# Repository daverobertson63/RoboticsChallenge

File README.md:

# RoboticsChallenge
Barclays Robotics Challenge - Main Code Repo

This is the main repo for the Barclays Remote Challenge and will work on any Unbutu style build

To install open a terminal window and make sure you are in /home/username - this is /home/roboteer

wget -N https://raw.githubusercontent.com/daverobertson63/RoboticsChallenge/master/brc.sh

chmod +x ./brc.sh

./brc.sh

Follow the instructions for either a local or remote refresh.  Local is the default one.

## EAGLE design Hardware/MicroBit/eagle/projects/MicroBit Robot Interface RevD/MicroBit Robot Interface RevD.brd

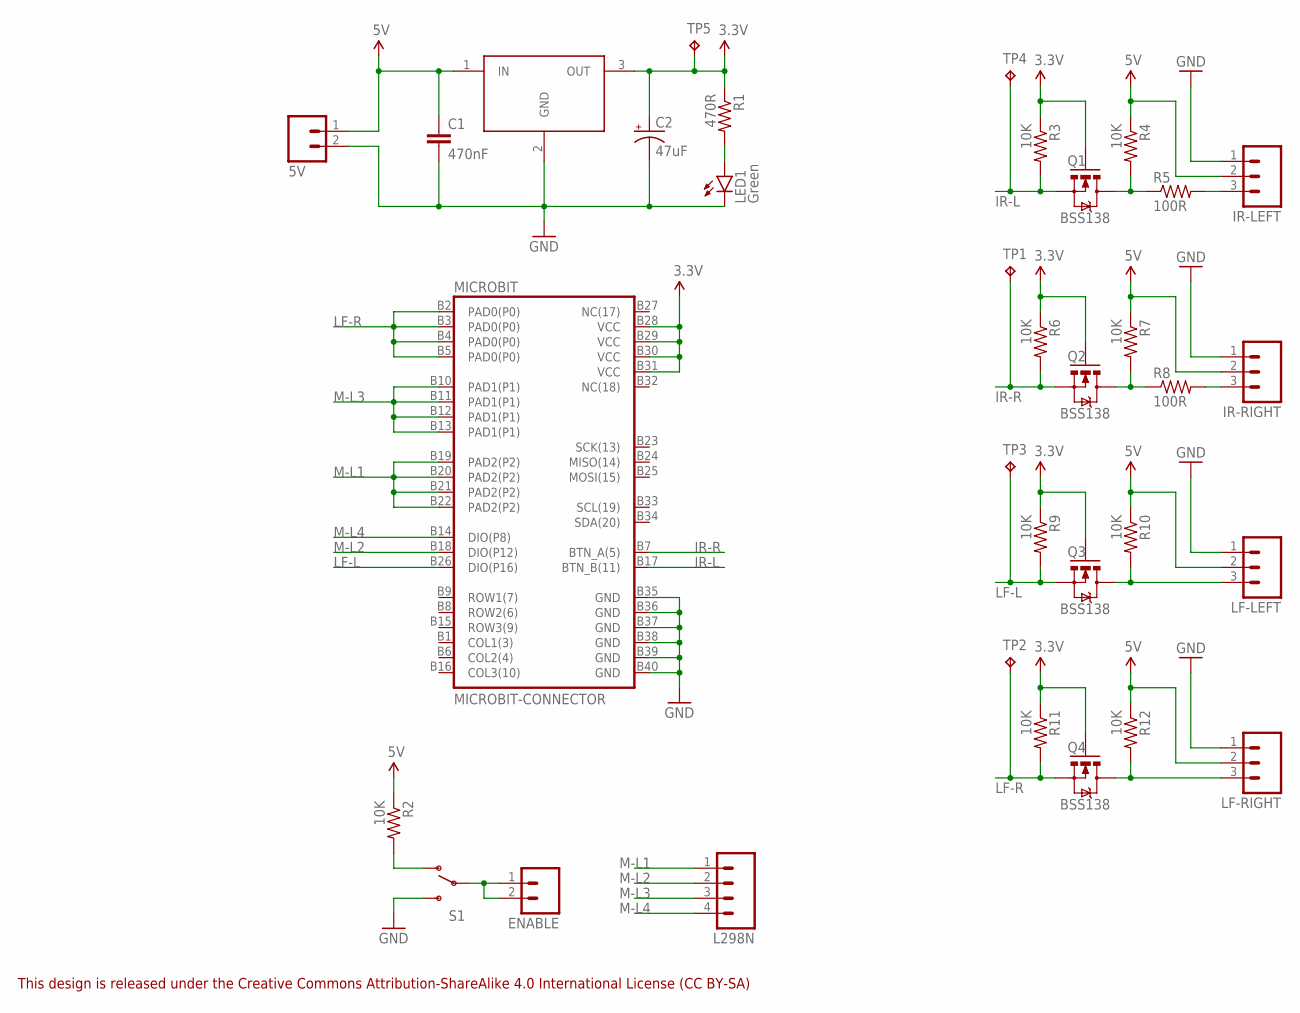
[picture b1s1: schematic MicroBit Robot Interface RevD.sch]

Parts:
5V: MCOMP_SCREWTERM_2PIN5MM; MCOMP-SCREWTERMINAL-5MM-2
C1: 470nF; 0603-CAP
C2: 47uF; CPOL-RADIAL-100UF-25V
ENABLE: M02PTH; 1X02
IR-LEFT: M03PTH; 1X03
IR-RIGHT: M03PTH; 1X03
L298N: M04PTH; 1X04
LED1: Green; LED3MM
LF-LEFT: M03PTH; 1X03
LF-RIGHT: M03PTH; 1X03
MICROBIT: MICROBIT-CONNECTOR; RBB40DHHN_MICROBIT
Q1, Q2, Q3, Q4: BSS138; SOT23-3
R1: 470R; 0603-RES
R2, R3, R4, R6, R7, R9, R10, R11, R12: 10K; 0603-RES
R5, R8: 100R; 0603-RES
S1: KNITTER-SWITCH-MFP106D
TP1, TP2, TP3, TP4, TP5: TPTP10R; TP10R
VR1: LM3940IMP-3.3; SOT223

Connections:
3.3V: C2.1 (+), MICROBIT.B28 (VCC), MICROBIT.B29 (VCC), MICROBIT.B30 (VCC), MICROBIT.B31 (VCC), Q1.1 (G), Q2.1 (G), Q3.1 (G), Q4.1 (G), R1.1, R3.1, R6.1, R9.1, R11.1, TP5.TP, VR1.3 (OUT)
5V: 5V.1, C1.1, IR-LEFT.2, IR-RIGHT.2, LF-LEFT.2, LF-RIGHT.2, R2.1, R4.1, R7.1, R10.1, R12.1, VR1.1 (IN)
GND: 5V.2, C1.2, C2.2 (-), IR-LEFT.1, IR-RIGHT.1, LED1.K (C), LF-LEFT.1, LF-RIGHT.1, MICROBIT.B35 (GND), MICROBIT.B36 (GND), MICROBIT.B37 (GND), MICROBIT.B38 (GND), MICROBIT.B39 (GND), MICROBIT.B40 (GND), S1.P$2 (POS2), VR1.2 (GND)
IR-L: MICROBIT.B17 (BTN_B(11)), Q1.2 (S), R3.2, TP4.TP
IR-R: MICROBIT.B7 (BTN_A(5)), Q2.2 (S), R6.2, TP1.TP
LF-L: MICROBIT.B26 (DIO(P16)), Q3.2 (S), R9.2, TP3.TP
LF-R: MICROBIT.B2 (PAD0(P0)), MICROBIT.B3 (PAD0(P0)), MICROBIT.B4 (PAD0(P0)), MICROBIT.B5 (PAD0(P0)), Q4.2 (S), R11.2, TP2.TP
M-L1: L298N.1, MICROBIT.B19 (PAD2(P2)), MICROBIT.B20 (PAD2(P2)), MICROBIT.B21 (PAD2(P2)), MICROBIT.B22 (PAD2(P2))
M-L2: L298N.2, MICROBIT.B18 (DIO(P12))
M-L3: L298N.3, MICROBIT.B10 (PAD1(P1)), MICROBIT.B11 (PAD1(P1)), MICROBIT.B12 (PAD1(P1)), MICROBIT.B13 (PAD1(P1))
M-L4: L298N.4, MICROBIT.B14 (DIO(P8))
unnamed: Q2.3 (D), R7.2, R8.1
unnamed: LF-LEFT.3, Q3.3 (D), R10.2
unnamed: LF-RIGHT.3, Q4.3 (D), R12.2
unnamed: R2.2, S1.P$1 (POS1)
unnamed: IR-LEFT.3, R5.2
unnamed: IR-RIGHT.3, R8.2
unnamed: Q1.3 (D), R4.2, R5.1
unnamed: LED1.A, R1.2
unnamed: ENABLE.1, ENABLE.2, S1.WIPER (COMMON)

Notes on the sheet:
This design is released under the Creative Commons Attribution-ShareAlike 4.0 International License (CC BY-SA)

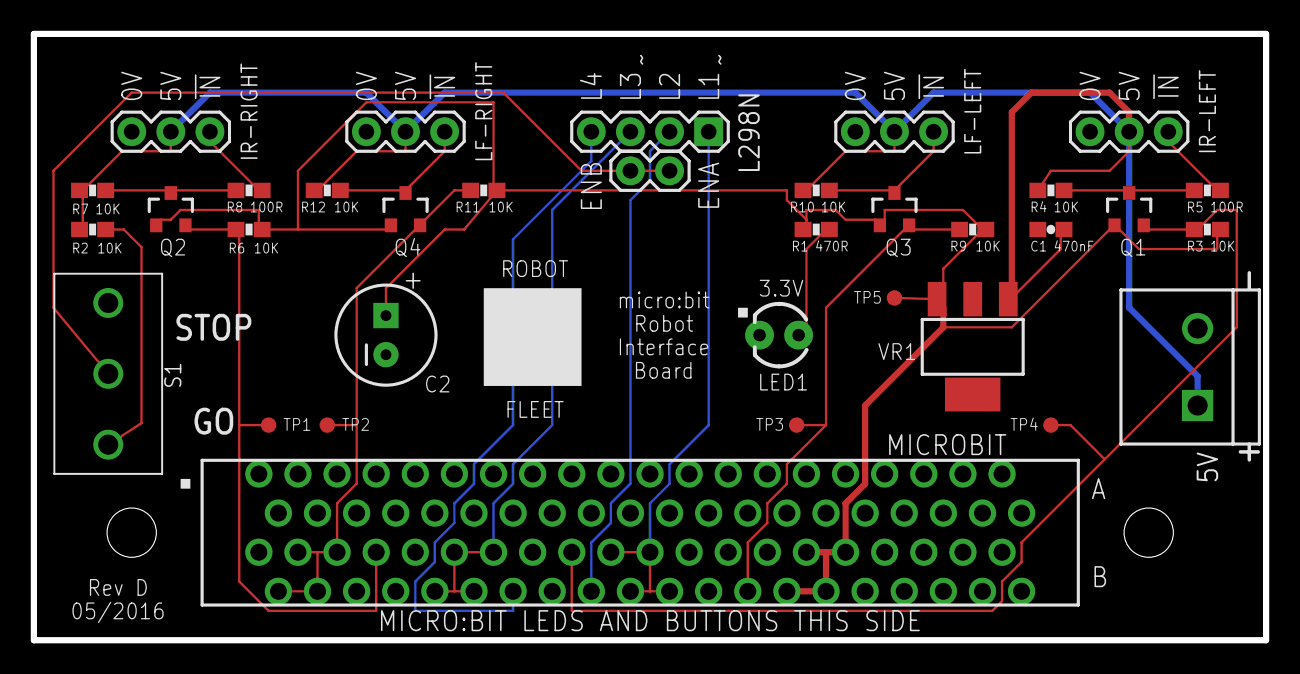
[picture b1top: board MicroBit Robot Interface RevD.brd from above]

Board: 2 copper layers, 80.0 x 39.4 mm, 34 parts (0 on the bottom side), 20 nets.

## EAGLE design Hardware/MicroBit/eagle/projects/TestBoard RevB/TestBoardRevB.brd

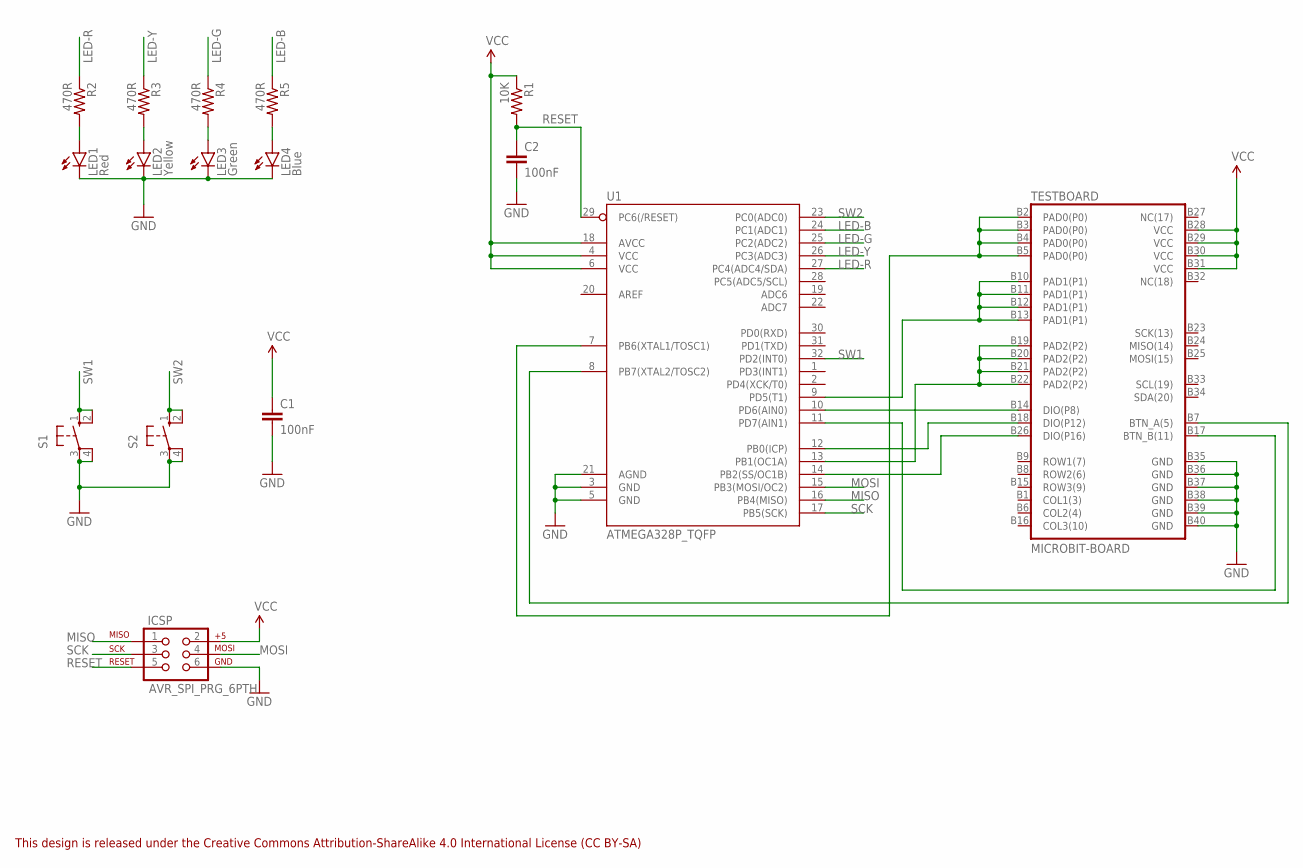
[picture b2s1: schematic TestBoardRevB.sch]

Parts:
C1, C2: 100nF; 0603-CAP
ICSP: AVR_SPI_PRG_6PTH; 2X3
LED1: Red; LED-0603
LED2: Yellow; LED-0603
LED3: Green; LED-0603
LED4: Blue; LED-0603
R1: 10K; 0603-RES
R2, R3, R4, R5: 470R; 0603-RES
S1, S2: 10-XX; B3F-10XX
TESTBOARD: MICROBIT-BOARD; MICROBIT-EDGE-CONN
U1: ATMEGA328P_TQFP; TQFP32-08

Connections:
GND: C1.2, C2.2, ICSP.6, LED1.C, LED2.C, LED3.C, LED4.C, S1.3, S1.4 (P1), S2.3, S2.4 (P1), TESTBOARD.B35 (GND), TESTBOARD.B36 (GND), TESTBOARD.B37 (GND), TESTBOARD.B38 (GND), TESTBOARD.B39 (GND), TESTBOARD.B40 (GND), U1.3 (GND), U1.5 (GND), U1.21 (AGND)
LED-B: R5.1, U1.24 (PC1(ADC1))
LED-G: R4.1, U1.25 (PC2(ADC2))
LED-R: R2.1, U1.27 (PC4(ADC4/SDA))
LED-Y: R3.1, U1.26 (PC3(ADC3))
MISO: ICSP.1, U1.16 (PB4(MISO))
MOSI: ICSP.4, U1.15 (PB3(MOSI/OC2))
unnamed: LED3.A, R4.2
unnamed: TESTBOARD.B2 (PAD0(P0)), TESTBOARD.B3 (PAD0(P0)), TESTBOARD.B4 (PAD0(P0)), TESTBOARD.B5 (PAD0(P0)), U1.7 (PB6(XTAL1/TOSC1))
unnamed: TESTBOARD.B7 (BTN_A(5)), U1.8 (PB7(XTAL2/TOSC2))
unnamed: TESTBOARD.B19 (PAD2(P2)), TESTBOARD.B20 (PAD2(P2)), TESTBOARD.B21 (PAD2(P2)), TESTBOARD.B22 (PAD2(P2)), U1.13 (PB1(OC1A))
unnamed: LED4.A, R5.2
unnamed: TESTBOARD.B10 (PAD1(P1)), TESTBOARD.B11 (PAD1(P1)), TESTBOARD.B12 (PAD1(P1)), TESTBOARD.B13 (PAD1(P1)), U1.9 (PD5(T1))
unnamed: LED1.A, R2.2
unnamed: TESTBOARD.B14 (DIO(P8)), U1.10 (PD6(AIN0))
unnamed: TESTBOARD.B18 (DIO(P12)), U1.12 (PB0(ICP))
unnamed: TESTBOARD.B26 (DIO(P16)), U1.14 (PB2(SS/OC1B))
unnamed: TESTBOARD.B17 (BTN_B(11)), U1.11 (PD7(AIN1))
unnamed: LED2.A, R3.2
RESET: C2.1, ICSP.5, R1.2, U1.29 (PC6(/RESET))
SCK: ICSP.3, U1.17 (PB5(SCK))
SW1: S1.1 (S), S1.2 (S1), U1.32 (PD2(INT0))
SW2: S2.1 (S), S2.2 (S1), U1.23 (PC0(ADC0))
VCC: C1.1, ICSP.2, R1.1, TESTBOARD.B28 (VCC), TESTBOARD.B29 (VCC), TESTBOARD.B30 (VCC), TESTBOARD.B31 (VCC), U1.4 (VCC), U1.6 (VCC), U1.18 (AVCC)

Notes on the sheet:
This design is released under the Creative Commons Attribution-ShareAlike 4.0 International License (CC BY-SA)

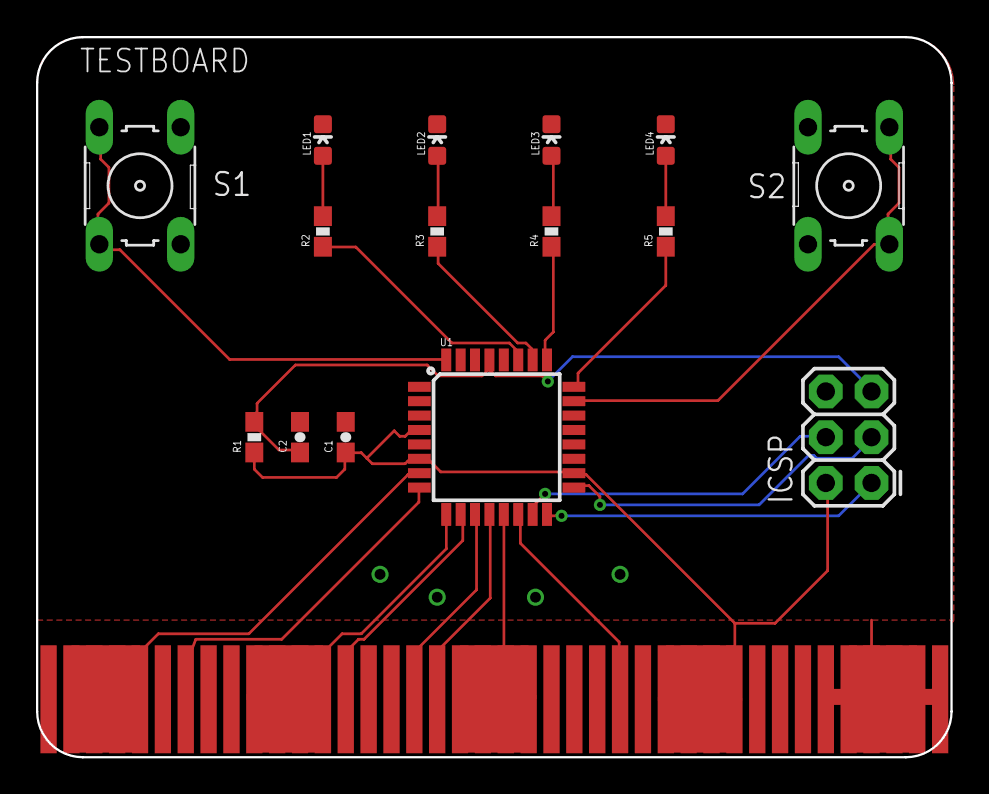
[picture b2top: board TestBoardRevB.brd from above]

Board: 2 copper layers, 50.8 x 40.0 mm, 16 parts (0 on the bottom side), 24 nets.

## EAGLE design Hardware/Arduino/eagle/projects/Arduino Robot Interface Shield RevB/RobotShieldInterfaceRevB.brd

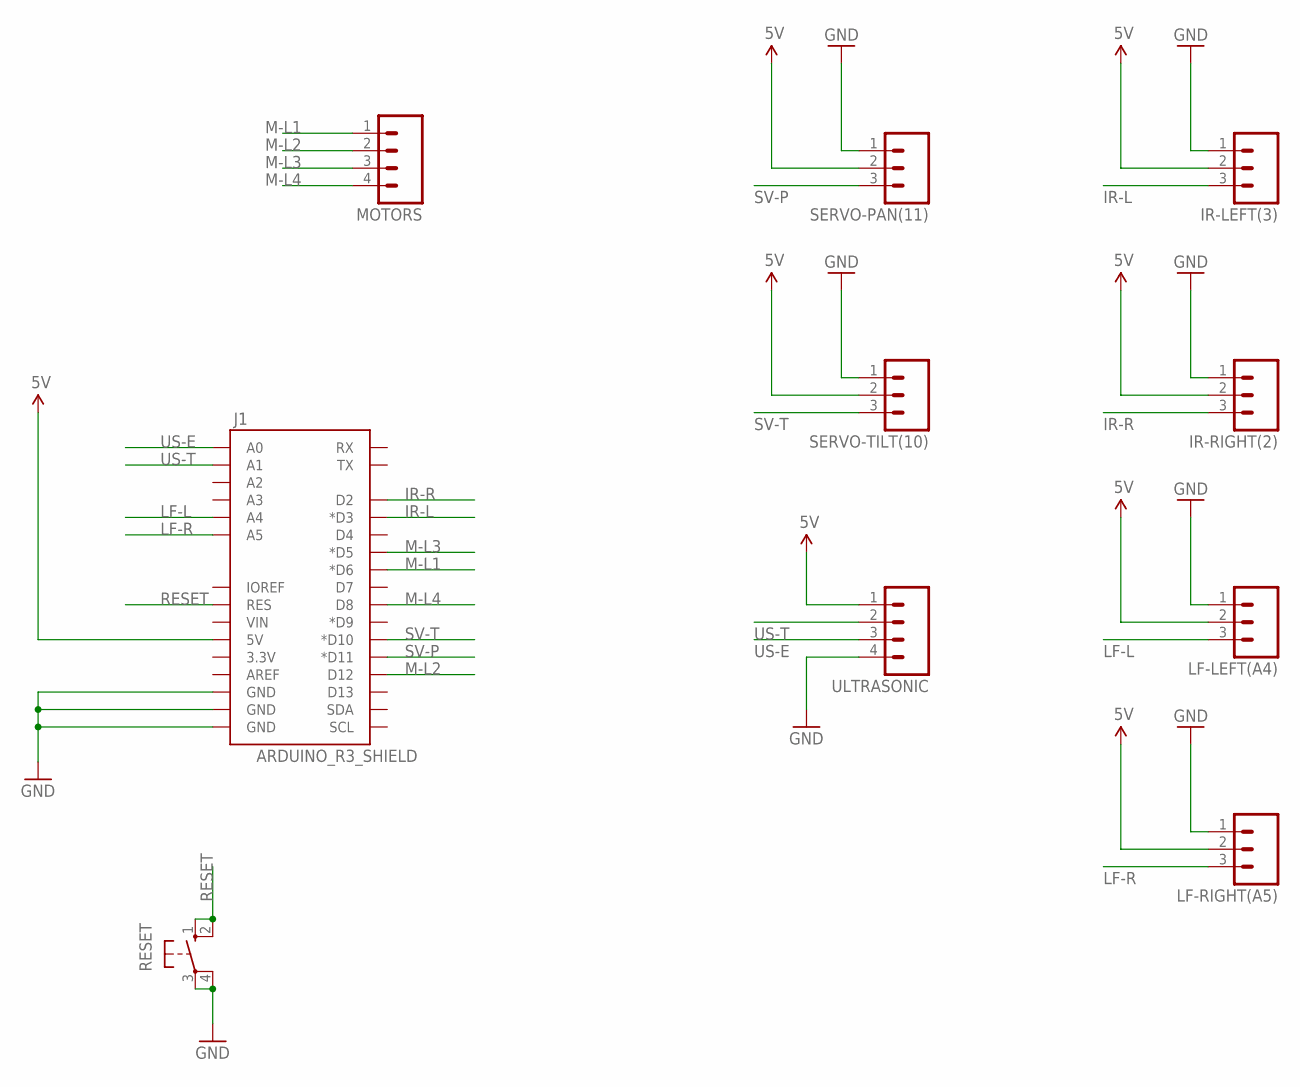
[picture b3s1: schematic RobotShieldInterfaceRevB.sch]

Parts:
IR-LEFT(3): M03PTH; 1X03
IR-RIGHT(2): M03PTH; 1X03
J1: ARDUINO_R3_SHIELD; UNO_R3_SHIELD
LF-LEFT(A4): M03PTH; 1X03
LF-RIGHT(A5): M03PTH; 1X03
MOTORS: M04PTH; 1X04
RESET: 10-XX; B3F-10XX
SERVO-PAN(11): M03PTH; 1X03
SERVO-TILT(10): M03PTH; 1X03
ULTRASONIC: M04PTH; 1X04

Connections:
5V: IR-LEFT(3).2, IR-RIGHT(2).2, J1.5V, LF-LEFT(A4).2, LF-RIGHT(A5).2, SERVO-PAN(11).2, SERVO-TILT(10).2, ULTRASONIC.1
GND: IR-LEFT(3).1, IR-RIGHT(2).1, J1.GND@0 (GND), J1.GND@1 (GND), J1.GND@2 (GND), LF-LEFT(A4).1, LF-RIGHT(A5).1, RESET.3, RESET.4 (P1), SERVO-PAN(11).1, SERVO-TILT(10).1, ULTRASONIC.4
IR-L: IR-LEFT(3).3, J1.D3 (*D3)
IR-R: IR-RIGHT(2).3, J1.D2
LF-L: J1.A4, LF-LEFT(A4).3
LF-R: J1.A5, LF-RIGHT(A5).3
M-L1: J1.D6 (*D6), MOTORS.1
M-L2: J1.D12, MOTORS.2
M-L3: J1.D5 (*D5), MOTORS.3
M-L4: J1.D8, MOTORS.4
RESET: J1.RES, RESET.1 (S), RESET.2 (S1)
SV-P: J1.D11 (*D11), SERVO-PAN(11).3
SV-T: J1.D10 (*D10), SERVO-TILT(10).3
US-E: J1.A0, ULTRASONIC.3
US-T: J1.A1, ULTRASONIC.2

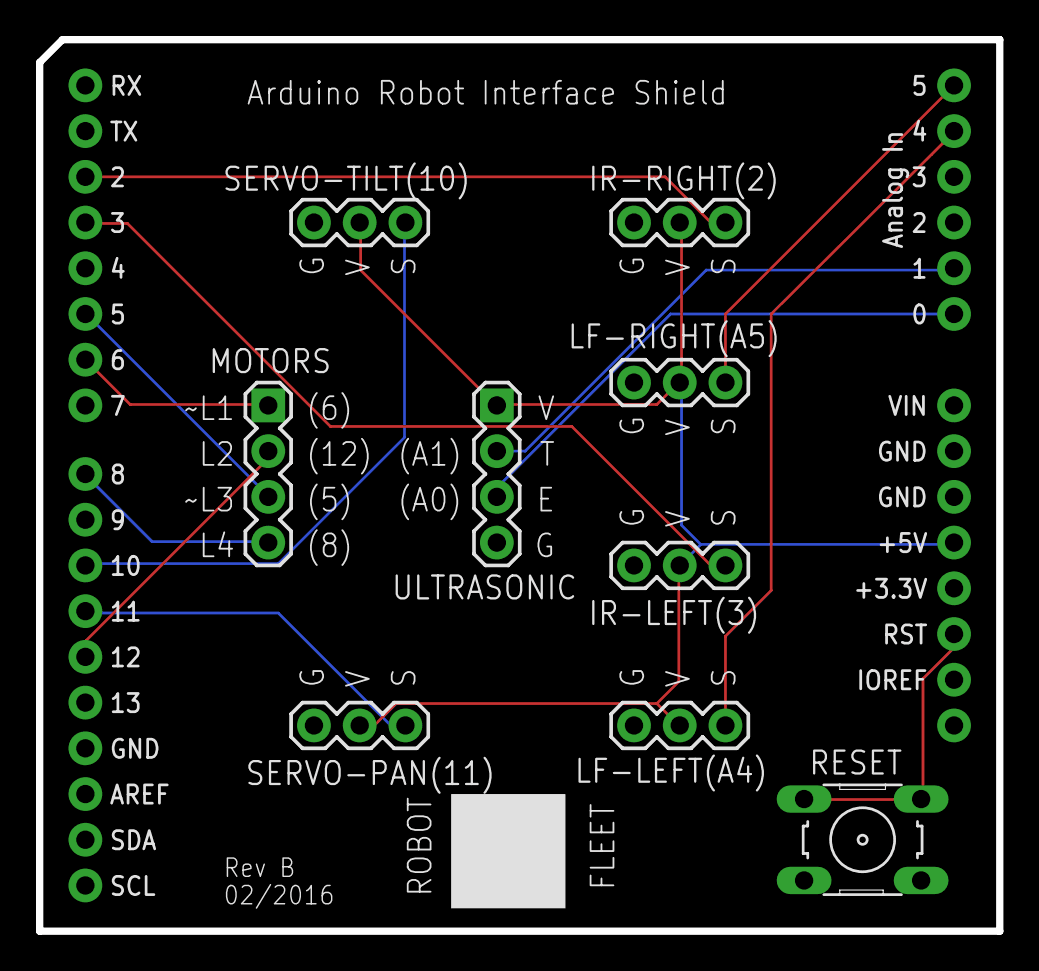
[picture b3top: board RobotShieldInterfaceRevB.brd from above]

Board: 2 copper layers, 53.3 x 49.5 mm, 10 parts (0 on the bottom side), 15 nets.

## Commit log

2015-04-07 Firstcut for all release docs
2015-04-13 Updated by simonwilmot to bug fix a couple of "features"
2015-04-30 Added new script for master
2015-04-30 Added more
2015-04-30 Beta version ready for tesging
2015-04-30 Bug fix 1
2015-04-30 Added readme
2015-04-30 Spelling in deskotp icon
2015-04-30 Fixed git install
2015-04-30 bug fixes
2015-04-30 More fixes
2015-04-30 Added Ballet and updated Goal
2015-04-30 Added auto install of git and pre check
2015-05-07 Updated line follower to have reversed LF
2015-05-08 Fixed bug in brc.sh
2016-02-05 Updated pins for new wiring to fix PWM issue.
2016-02-10 First version of interface and test board designs
    MicroBit robot interface board Rev A and Test Board Rev A Eagle files,
    Test Board Arduino config files and test sketch.
2016-02-12 MicroBit interface board documentation
2016-03-14 Updated for production Micro:Bit hardware
    Updated for first production Micro:Bit release (with Button A on Pin 5).
    See https://www.microbit.co.uk/device/pins.
    Updated MicroBit custom library to v0.2.
    Move Button A from pin 4 to pin 5 and swap over P1 and P8 on L3 and L4
    on robot interface board for PWM support.
    Relocate the enable switch to the edge of the board.
2016-03-30 Update to microbit board rev C
    Reorganise the hardware into a single folder. Update the micro:bit
    interface board to Rev C with fix to switch orientation, additional test
    points. Gerbers for OSH Park and SeeedStudio. Update documentation with
    test plan.
2016-05-10 Production micro:bit interface board
    Documentation updates, wiring diagrams added, board images added. Also
    Gerbers for Arduino shield updated with OSH Park and SeeedStudio
    versions.
2016-05-15 Minor board mods
    Increased power traces to 16mil throughout.
2016-06-08 Fixed spin functions and other minor bug fixes
2016-06-10 Centre the head in setup
2016-06-26 Updated docs

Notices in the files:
parts and their libraries:
SparkFun-Connectors: Licensing: Creative Commons ShareAlike 4.0 International - https://creativecommons.org/licenses/by-sa/4.0
